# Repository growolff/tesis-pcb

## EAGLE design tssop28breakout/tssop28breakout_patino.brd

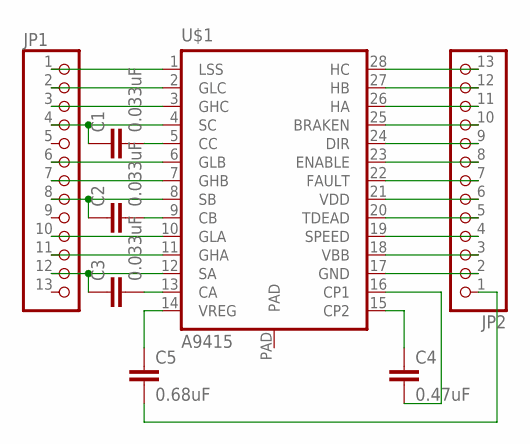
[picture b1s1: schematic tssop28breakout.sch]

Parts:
C1, C2, C3: 0.033uF; C0805
C4: 0.47uF; C0805
C5: 0.68uF; C0805
JP1, JP2: PINHD-1X13_BIG; 1X13-BIG
U$1: A9415; TSSOP28

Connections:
GND: JP2.2, U$1.17 (GND)
unnamed: JP1.1, U$1.1 (LSS)
unnamed: JP1.2, U$1.2 (GLC)
unnamed: JP1.3, U$1.3 (GHC)
unnamed: C1.1, JP1.4, U$1.4 (SC)
unnamed: C3.2, U$1.13 (CA)
unnamed: JP1.6, U$1.6 (GLB)
unnamed: JP1.7, U$1.7 (GHB)
unnamed: C2.1, JP1.8, U$1.8 (SB)
unnamed: C2.2, U$1.9 (CB)
unnamed: JP1.10, U$1.10 (GLA)
unnamed: JP1.11, U$1.11 (GHA)
unnamed: C3.1, JP1.12, U$1.12 (SA)
unnamed: C1.2, U$1.5 (CC)
unnamed: C5.1, U$1.14 (VREG)
unnamed: JP2.13, U$1.28 (HC)
unnamed: JP2.12, U$1.27 (HB)
unnamed: JP2.11, U$1.26 (HA)
unnamed: JP2.10, U$1.25 (BRAKEN)
unnamed: JP2.9, U$1.24 (DIR)
unnamed: JP2.8, U$1.23 (ENABLE)
unnamed: JP2.7, U$1.22 (FAULT)
unnamed: JP2.6, U$1.21 (VDD)
unnamed: JP2.5, U$1.20 (TDEAD)
unnamed: JP2.4, U$1.19 (SPEED)
unnamed: JP2.3, U$1.18 (VBB)
unnamed: C4.1, U$1.15 (CP2)
unnamed: C4.2, U$1.16 (CP1)
unnamed: C5.2, JP2.1
PAD: U$1.PAD

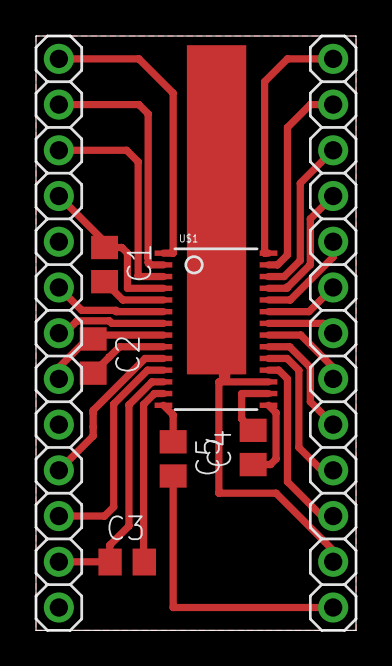
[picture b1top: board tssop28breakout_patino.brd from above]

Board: 2 copper layers, 17.8 x 33.0 mm, 8 parts (0 on the bottom side), 29 nets.
